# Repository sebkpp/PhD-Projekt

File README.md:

# Collaborative Manual Tasks in Distributed Virtual Environments

A PhD research project investigating multisensory feedback strategies for collaborative object handovers in VR. Two participants wearing VR headsets share a virtual workspace and pass surgical instruments to each other while different visual, auditory, and tactile feedback conditions are applied. The goal is to identify which feedback combinations best support safe and effective handovers.

---

## Repository Structure

```
projekt_ws24/
├── Unity/          VR application (C#, Photon Fusion, OpenXR)
├── Web/            Study management & analysis platform (Python/FastAPI + React)
├── sql/            PostgreSQL database schema
└── notebooks/      Data analysis notebooks (Jupyter, planned)
```

| Subsystem | Description | README |
|---|---|---|
| **Unity** | Multiplayer VR app — runs on two Meta Quest headsets simultaneously | [Unity/README.md](Unity/README.md) |
| **Web** | Browser-based platform for configuring studies, controlling sessions, and analysing results | [Web/README.md](Web/README.md) |
| **SQL** | Database schema reference — all tables with descriptions | [sql/README.md](sql/README.md) |
| **Notebooks** | Jupyter notebooks for statistical analysis and visualisation of study data | [notebooks/README.md](notebooks/README.md) |

---

## Architecture

```
┌─────────────────────────────────────────────────────────────┐
│  Unity VR Application (×2 headsets)                         │
│  Photon Fusion (multiplayer) · OpenXR · Meta Quest          │
│  Reports handover events and eye tracking via REST          │
└──────────────────────┬──────────────────────────────────────┘
                       │ HTTP/REST
┌──────────────────────▼──────────────────────────────────────┐
│  Web Backend  (FastAPI · Python 3.12 · port 5000)           │
│  Business logic · REST API · DB access via SQLAlchemy       │
└──────────────────────┬──────────────────────────────────────┘
                       │ SQLAlchemy / psycopg2
┌──────────────────────▼──────────────────────────────────────┐
│  PostgreSQL 17  (port 5432)                                  │
│  Studies · Experiments · Trials · Handovers · Eye Tracking  │
└─────────────────────────────────────────────────────────────┘
                       ▲
                       │ REST API  (/api → port 5000)
┌──────────────────────┴──────────────────────────────────────┐
│  Web Frontend  (React · Vite · port 5173)                   │
│  Study configuration · Live session control · Analysis UI   │
└─────────────────────────────────────────────────────────────┘
```

**Data flow during a study session:**

1. Researcher configures a study (stimuli, questionnaires, participant slots) in the web frontend.
2. The Unity application polls the backend for the active experiment and loads the assigned stimulus configuration.
3. During the trial, Unity sends handover events and eye tracking fixations to the backend in real time.
4. After each trial, participants fill in questionnaires via the web frontend.
5. After the study, the researcher accesses the analysis section to review results and export data.

---

## Quick Start

See [Web/README.md](Web/README.md) for full setup and start instructions. The short version:

```bash
# Windows — one-time setup
Web\setup_windows.bat

# macOS — one-time setup
chmod +x Web/setup_mac.sh && ./Web/setup_mac.sh

# Start both backend and frontend
Web\start_windows.bat      # Windows
./Web/start_mac.sh         # macOS
```

Open **http://localhost:5173** in your browser.

---

## Branch Strategy

| Branch | Purpose |
|---|---|
| `main` | Stable releases — only receives merges from `development` |
| `development` | Integration branch — all feature and fix branches merge here first |
| `feature/*` | New features, branched off `development` |
| `fix/*` | Bug fixes, branched off `development` |

New work is always branched from `development`. Once a set of changes has been tested and is considered stable, `development` is merged into `main`. Never commit directly to `main`.

---

## Tech Stack

| Layer | Technology |
|---|---|
| VR Runtime | Unity, C#, Photon Fusion 2 (Shared Mode), OpenXR |
| Backend | Python 3.12, FastAPI, SQLAlchemy, uv |
| Frontend | React, Vite, MUI, Ant Design, Tailwind CSS, react-i18next (DE/EN) |
| Database | PostgreSQL 17 |
| Charts | Recharts, Chart.js, ApexCharts, Plotly |

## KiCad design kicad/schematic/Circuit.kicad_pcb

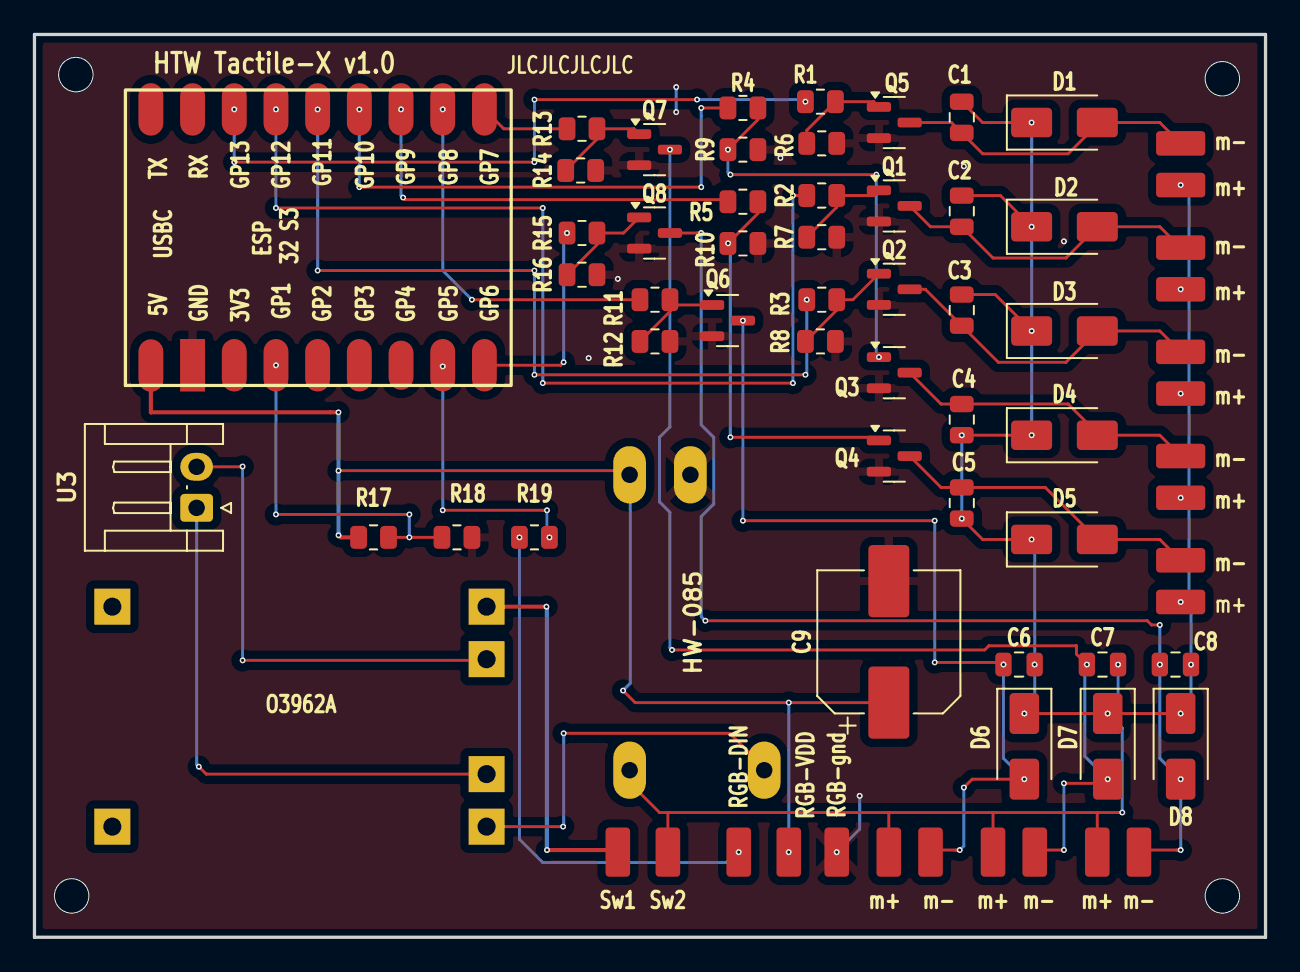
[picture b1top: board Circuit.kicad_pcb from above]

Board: 2 copper layers, 75.0 x 55.0 mm, 69 parts (0 on the bottom side), 34 nets.

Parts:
C1, C2, C3, C4, C5, C6, C7, C8: C; C_0805_2012Metric
C9: C_Polarized; CP_Elec_8x10.5
D1, D2, D3, D4, D5, D6, D7, D8: SS14; D_SMA
ESP32_S3_ZERO1: ESP32-S3-ZERO
HW-085: HW-085
O3962A: O3962A Battery IC
Q1, Q2, Q3, Q4, Q5, Q6, Q7, Q8: AO3400A; SOT-23
R2, R3, R4, R5, R6, R7, R8, R9, R10, R11, R12, R13, R14, R15, R16, R17, R18, R19: R; R_0805_2012Metric
RGB-DIN: blank pad
RGB-VDD: blank pad
RGB-gnd: blank pad
RL1: R; R_0805_2012Metric
Sw1, Sw2: blank pad
U3: JST-PH2; JST_EH_S2B-EH_1x02_P2.50mm_Horizontal
m+: blank pad
m+#2, m+#3, m+#4, m+#5, m+#6, m+#7, m+#8: blank pad
m-: blank pad
m-#2, m-#3, m-#4, m-#5, m-#6, m-#7, m-#8: blank pad

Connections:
GND: C9.2, ESP32_S3_ZERO1.2 (GND), HW-085.2 (OUT_-), Q1.2 (S), Q2.2 (S), Q3.2 (S), Q4.2 (S), Q5.2 (S), Q6.2 (S), Q7.2 (S), Q8.2 (S), R6.2, R7.2, R8.2, R9.2, R10.2, R12.2, R14.2, R16.2, R18.1, RGB-gnd.1 (pin)
GND1: HW-085.4 (IN_-), O3962A.6 (Out-)
unnamed: O3962A.2 (Battery+), U3.2
unnamed: O3962A.3 (Battery-), U3.1
unnamed: C1.1, D1.2 (A), Q5.3 (D), m-#2.1 (pin)
unnamed: C1.2, C2.2, C3.2, C4.2, C5.2, C6.2, C7.2, C8.2, D1.1 (K), D2.1 (K), D3.1 (K), D4.1 (K), D5.1 (K), D6.1 (K), D7.1 (K), D8.1 (K), HW-085.3 (IN_+), Sw2.1 (pin), m+.1 (pin), m+#2.1 (pin), m+#3.1 (pin), m+#4.1 (pin), m+#5.1 (pin), m+#6.1 (pin), m+#7.1 (pin), m+#8.1 (pin)
unnamed: C2.1, D2.2 (A), Q1.3 (D), m-#5.1 (pin)
unnamed: C3.1, D3.2 (A), Q2.3 (D), m-#4.1 (pin)
unnamed: C4.1, D4.2 (A), Q3.3 (D), m-#6.1 (pin)
unnamed: C5.1, D5.2 (A), Q4.3 (D), m-.1 (pin)
unnamed: C6.1, D6.2 (A), Q6.3 (D), m-#8.1 (pin)
unnamed: C7.1, D7.2 (A), Q7.3 (D), m-#3.1 (pin)
unnamed: C8.1, D8.2 (A), Q8.3 (D), m-#7.1 (pin)
unnamed: C9.1, ESP32_S3_ZERO1.1 (5V), HW-085.1 (OUT_+), R17.1, RGB-VDD.1 (pin)
unnamed: ESP32_S3_ZERO1.4 (GP1), R17.2, R18.2
unnamed: ESP32_S3_ZERO1.8 (GP5), R19.1
unnamed: ESP32_S3_ZERO1.9 (GP6), R15.2
unnamed: ESP32_S3_ZERO1.10 (GP7), R13.2
unnamed: ESP32_S3_ZERO1.11 (GP8), R11.2
unnamed: ESP32_S3_ZERO1.12 (GP9), R5.2
unnamed: ESP32_S3_ZERO1.13 (GP10), R4.2
unnamed: ESP32_S3_ZERO1.14 (GP11), R3.2
unnamed: ESP32_S3_ZERO1.15 (GP12), R2.2
unnamed: ESP32_S3_ZERO1.16 (GP13), RL1.2
unnamed: Q1.1 (G), R2.1, R7.1
unnamed: Q2.1 (G), R3.1, R8.1
unnamed: Q3.1 (G), R4.1, R9.1
unnamed: Q4.1 (G), R5.1, R10.1
unnamed: Q5.1 (G), R6.1, RL1.1
unnamed: Q6.1 (G), R11.1, R12.1
unnamed: Q7.1 (G), R13.1, R14.1
unnamed: Q8.1 (G), R15.1, R16.1
unnamed: R19.2, RGB-DIN.1 (pin)
unnamed: O3962A.5 (OUT+), Sw1.1 (pin)

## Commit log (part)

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2026-03-14 feat: add CSV/XLSX export endpoints and export_service for handover data
    Adds export_service.py with export_handovers_csv/xlsx helpers, two new
    GET endpoints (/analysis/study/{id}/export/csv|xlsx) in analysis.py, and
    get_handovers_by_study to HandoverRepository for the study-level join.
2026-03-14 feat: add inferentialAnalysisService.js with all analysis API calls and file download helpers
2026-03-14 feat: add CrossStudyChart, AnalysisDashboard page, and analysis link in StudyTile
2026-03-15 docs: update analysis UI integration spec to v3
    - Correct study design: experiment level = descriptive only (pseudoreplication)
    - Move inferential display to StudyAnalysisPage only
    - Add Bonferroni post-hoc and all effect sizes (Cohen's d, Cliff's Delta, η²p, ω²p, Kendall's W) status
    - Add questionnaire service migration section (run_paired_test → run_inferential_analysis)
    - Split into Session A (integration) and Session B (new charts) with placeholders
    - Add PPI metric explanation and 3 new backend endpoints
2026-03-15 feat: migrate questionnaire analysis to N-condition inferential tests
2026-03-15 fix: use datetime.min fallback for None starttimes in ET transition sort
2026-03-15 feat: add PlaceholderChart and refactor ExperimentAnalyseTabs to CSS visibility
2026-03-15 feat: restructure ExperimentAnalysisPage with lazy tabs, descriptive analysis, and Session B placeholders
2026-03-15 docs: add Performance Charts Session B design spec
2026-03-15 docs: clarify handovers_by_trial insertion point in performance spec
2026-03-15 feat: add ErrorRateBar chart component
2026-03-15 docs: add ET charts Session B design spec
2026-03-15 docs: fix ET charts spec — second guard, unconditional EyeTrackingCharts render
2026-03-15 feat: add saccade-rate endpoint for experiment eye-tracking
2026-03-15 feat: add SaccadeRateBar Recharts component
2026-03-15 fix: hoist darkLayout to module scope, use reduce for globalZMax
2026-03-15 docs: add UX charts Session B design spec
2026-03-15 feat: add trial_number to compute_trial_item_stats response
2026-03-15 feat: add AttrakDiffPortfolio scatter chart (PQ vs ATT)
2026-03-15 feat: integrate NASA-TLX, SUS, AttrakDiff2 charts into QuestionnaireCharts
2026-03-18 feat: reduce avatar visibility to single full-body entry
2026-03-18 feat: add PATCH /handovers/{id}/phases endpoint
2026-03-18 feat: add POST /eyetracking endpoint with FK validation and tests
    Adds eyetracking router with explicit 404 checks for handover_id,
    participant_id, and aoi_id; registers it in routes/__init__.py;
    adds 5 pytest tests covering success and all FK-not-found cases.
    Also renames the hanover_id typo column to handover_id in both
    testdb and production DB eye_tracking table to match the ORM model.
2026-03-21 feat: add jupyterlab, ipykernel, seaborn as optional notebook dependencies
2026-03-21 fix: correct questionnaire_response study_id filter join
2026-03-22 fix: untrack .env and .env.test from git index
    Files were accidentally tracked despite being listed in .gitignore.
    Credentials must never be stored in version control.
2026-03-22 feat: add coverage report to GitHub Actions job summary
2026-03-22 docs: add analysis service coverage design spec
2026-03-22 docs: fix spec inaccuracies found in third review pass
2026-03-22 test: add db_session, seed_aoi, trial_id, handover_id fixtures to conftest
2026-03-22 test: add unit tests for questionnaire analysis pandas helpers
2026-03-22 test: add direct service-level tests for study stimuli and questionnaire paths
2026-03-22 test: add diagnostic message to pre-existing len assertion in test_study
2026-03-24 refactor: fix naming, field grouping and material usage in NetworkRig debug support
2026-03-24 refactor: migrate GrabHand to modern Avatar namespace
2026-03-24 refactor: migrate PassableObject to modern NetworkRig and add namespace
2026-03-24 refactor: fix naming, side-effecting getter and async exception handling in ConnectionManager
2026-03-25 feat: add leg offset fields to AvatarConfig (Utils winner)
2026-03-25 feat: add Utils.FingerOffsets overload to AvatarFingerJointMap
2026-03-25 feat: port RotationFromAngularVelocity and VelocityFollow to VelocityExtension
2026-03-25 refactor: remove unused imports from PassableObject
2026-03-25 refactor: standardize Utils namespace and fix AvatarSpawner Singleton import
2026-03-26 refactor: replace PlayerManager with Fusion 2 Shared Mode IPlayerJoined/IPlayerLeft implementation
2026-03-26 refactor: DataManager receives localPlayerId via SetLocalPlayerId, removes GameManager dependency
2026-03-26 refactor: delete obsolete PlayerObject
2026-03-27 refactor: move ManagerUI to GUI folder, update namespace
2026-03-27 refactor: update Avatar joint map namespaces, remove Grasp interaction scripts
2026-03-27 feat: add App assets (Scenes, Prefabs, Models, Config, Materials, SFX, Sprites)
2026-03-27 chore: add missing App folder/subfolder meta files and remaining script stubs
2026-03-27 fix: remove files re-introduced by merge that were deleted in feature branch
    GameManager, PlayerObject, AvatarSpawner, GrabHand and GraspableObject
    were explicitly deleted during feature/connection-player-refactor but
    accidentally re-introduced when merging into development.
2026-03-27 docs: add avatar direct-drive refactor design spec
2026-03-27 feat: add Metacarpal field to FingerState
2026-03-27 feat: add ArmIKSolver with analytic 2-bone IK and EditMode tests
2026-03-27 feat: add AvatarDriver - direct bone driver for head, body, fingers, and arms
2026-03-27 feat: add Metacarpal joint to FingerStateNetworked for network sync
2026-03-27 chore: remove stale HardwareHand, update Grabber.cs to Hardware namespace, delete TrackingData
2026-03-28 fix: restore AvatarHand on NetworkHand, update NetworkedGrabbable and PlayerVisuals
2026-03-28 fix: address code review issues - frame-dedup body drive, network HandState write, null guards
2026-03-28 fix: add Unity.XR.Hands reference to editor asmdef for HandCalibrationTool
2026-03-28 fix: add missing meta files, namespace usings, and gitignore for docs/plans
    - Add .gitignore to exclude docs/plans/ from version control
    - Fix missing using statements in HardwareHand, HandCalibrationTool, PlayerVisualsEditor
    - Remove de.htw.handtrackvr package from manifest
    - Add all missing .meta files for new Avatar subfolders (Data, Driver, Hardware, Mapping, Visuals)
    - Add HardwareHeadset.cs and RigPart.cs with their metas
    - Remove duplicate ArmIKSolverTests.cs from wrong EditMode/Avatar/ path
2026-03-28 test: make skips_started test deterministic
2026-03-28 feat: add AvatarSet ScriptableObject with EditMode tests
2026-03-28 refactor: PlayerVisuals uses AvatarSet + SetGender instead of Resources.LoadAll
2026-03-28 feat: add ExperimentContext — fetches next open experiment from backend
2026-03-28 fix: remove AvatarScriptableObject from HandCalibrationTool, null-guards and event conventions
2026-03-29 feat: add GripType enum and GrabSettings ScriptableObject
2026-03-29 feat: add GrabHand with fingertip colliders and grip threshold detection
2026-03-29 feat: add HandoverTracker with 4 study events via Fusion RPC
2026-03-29 chore: Unity Editor setup — GrabSettings asset, PlayerAvatar cleanup, XR Rig
2026-03-29 fix: add trailing newline to experiment_service.py
2026-03-29 feat: add C# events to HandoverTracker alongside Fusion RPCs
2026-03-29 feat: add HandoverReporter to persist handover events via HTTP
2026-03-29 fix: handle drop during POST in-flight and add ExperimentContext null guard in HandoverReporter
2026-03-29 chore: add HandoverReporter component to Block_Original prefab
2026-04-02 perf: replace Fresnel GPU branch with branchless math in MirrorReflection shader
2026-04-03 chore: stage all pending changes across Mirror and App
    Includes Mirror script/shader/scene additions, app script updates
    (HandoverReporter, AvatarSet, PlayerVisuals, GazeInputController,
    ReCenter, ManagerUI, Log, PushButtonFeedback, NetworkedGrabbable),
    deleted obsolete prefabs (Constraints, Network, PlayerManager) and
    scripts (NetworkFinger, CustomExtensions stubs), package updates,
    and renderer/tag-manager settings.
2026-04-03 ci: remove deprecated unity-request-activation-file workflow
2026-04-03 chore: delete obsolete AvatarScriptableObject and casual avatar assets
2026-04-05 fix: use TrialSlotRepository, add 404 guard, fix imports in stimuli endpoint
    - Move TrialSlot import to module level in trial_service.py
    - Replace raw session.query with TrialSlotRepository.get_by_trial_id
    - Add order_by(TrialSlot.slot) to TrialSlotRepository.get_by_trial_id
    - Add trial existence check in get_stimuli_for_trial, raise ValueError on missing trial
    - Catch ValueError in stimuli route and return HTTP 404 for trial_not_found
    - Ensure all modified files end with a newline
2026-04-05 test: add tests for stimuli in /experiments/next response
2026-04-05 chore: add Unity .meta files for feedback system
2026-04-05 feat: add StimulusConfigLoader with HTTP fetch
2026-04-05 feat: add ToneAuditoryFeedback and TactileFeedbackPlaceholder
2026-04-05 fix: update PlayerVisualsEditor to use renamed AvatarInitialized field
2026-04-05 chore: add missing .meta files for Feedback subfolder structure
2026-04-05 feat: add feedback components to PlayerAvatar prefab
2026-04-06 test: add EditMode tests for ToneAuditoryFeedback and HandRenderingController
2026-04-06 feat: add SessionState DTO with EditMode tests
2026-04-06 feat: add StudySessionConfig ScriptableObject
2026-04-06 refactor: migrate PlayerManager from ExperimentContext to BackendService
2026-04-06 refactor: delete ExperimentContext, StimulusConfigLoader, WebConnection
2026-04-06 refactor: remove redundant playerId from SlotConfig, derive from array index
2026-04-06 refactor: remove unused package dependencies from manifest and packages-lock
2026-04-07 refactor: GrabHand grabs Grabbable directly, NetworkGrabbableObject is optional hook
2026-04-07 feat: add OnTrialStarted/OnTrialEnded events to ExperimentController
2026-04-07 fix: guard against null _handoverTrackers in SceneSetup.Awake
2026-04-07 fix: add missing using for PlayerVisuals, remove redundant qualifier in NetworkHand
2026-05-01 docs: restructure READMEs across repository
    - Root README: project scope, architecture diagram, quick start, tech stack
    - Web/README: replace project description with link to root, add Web Architecture section
    - sql/README: document all database tables with descriptions
    - notebooks/README: note planned Jupyter notebooks for data analysis
    - .gitignore: replace partial docs/ entries with single docs/ rule
    - Remove docs/specs/ from git tracking (docs/ is now gitignored)
2026-05-15 Added grabbing test scene and non-networked block prefab variants
2026-05-15 feat: add Netzwerk test scene (Presence + Multiplayer)
2026-05-15 feat: add Vollstaendig production scene and session_LocalOnline config
2026-05-15 feat: install react-i18next and configure i18n
2026-05-15 feat(i18n): add navigation namespace, update breadcrumb labels
2026-05-15 feat(i18n): add experiment namespace
2026-05-15 feat(i18n): add participant namespace
2026-05-15 feat(i18n): add questionnaire namespace translations to waiting component
2026-05-15 feat(i18n): complete frontend localization DE/EN
2026-05-15 feat(i18n): localize validation messages in demography, questionnaire, and config hooks
2026-05-15 feat(i18n): move language switcher into breadcrumb bar
2026-05-15 feat: complete systematic i18n localization pass
    Harvested all remaining hardcoded German strings across 17 components.
    Added locale keys to questionnaire, experiment, overview, configuration,
    common, and navigation namespaces (de + en). Timeline phase labels are
    now translated while keeping German state identifiers for comparisons.
2026-05-15 docs(unity): fix scene names in README to match actual scene files
2026-05-15 added baked lightmaps for operational room
2026-05-17 fix: bugfixes in UI and localizations
2026-05-17 added docs/images
